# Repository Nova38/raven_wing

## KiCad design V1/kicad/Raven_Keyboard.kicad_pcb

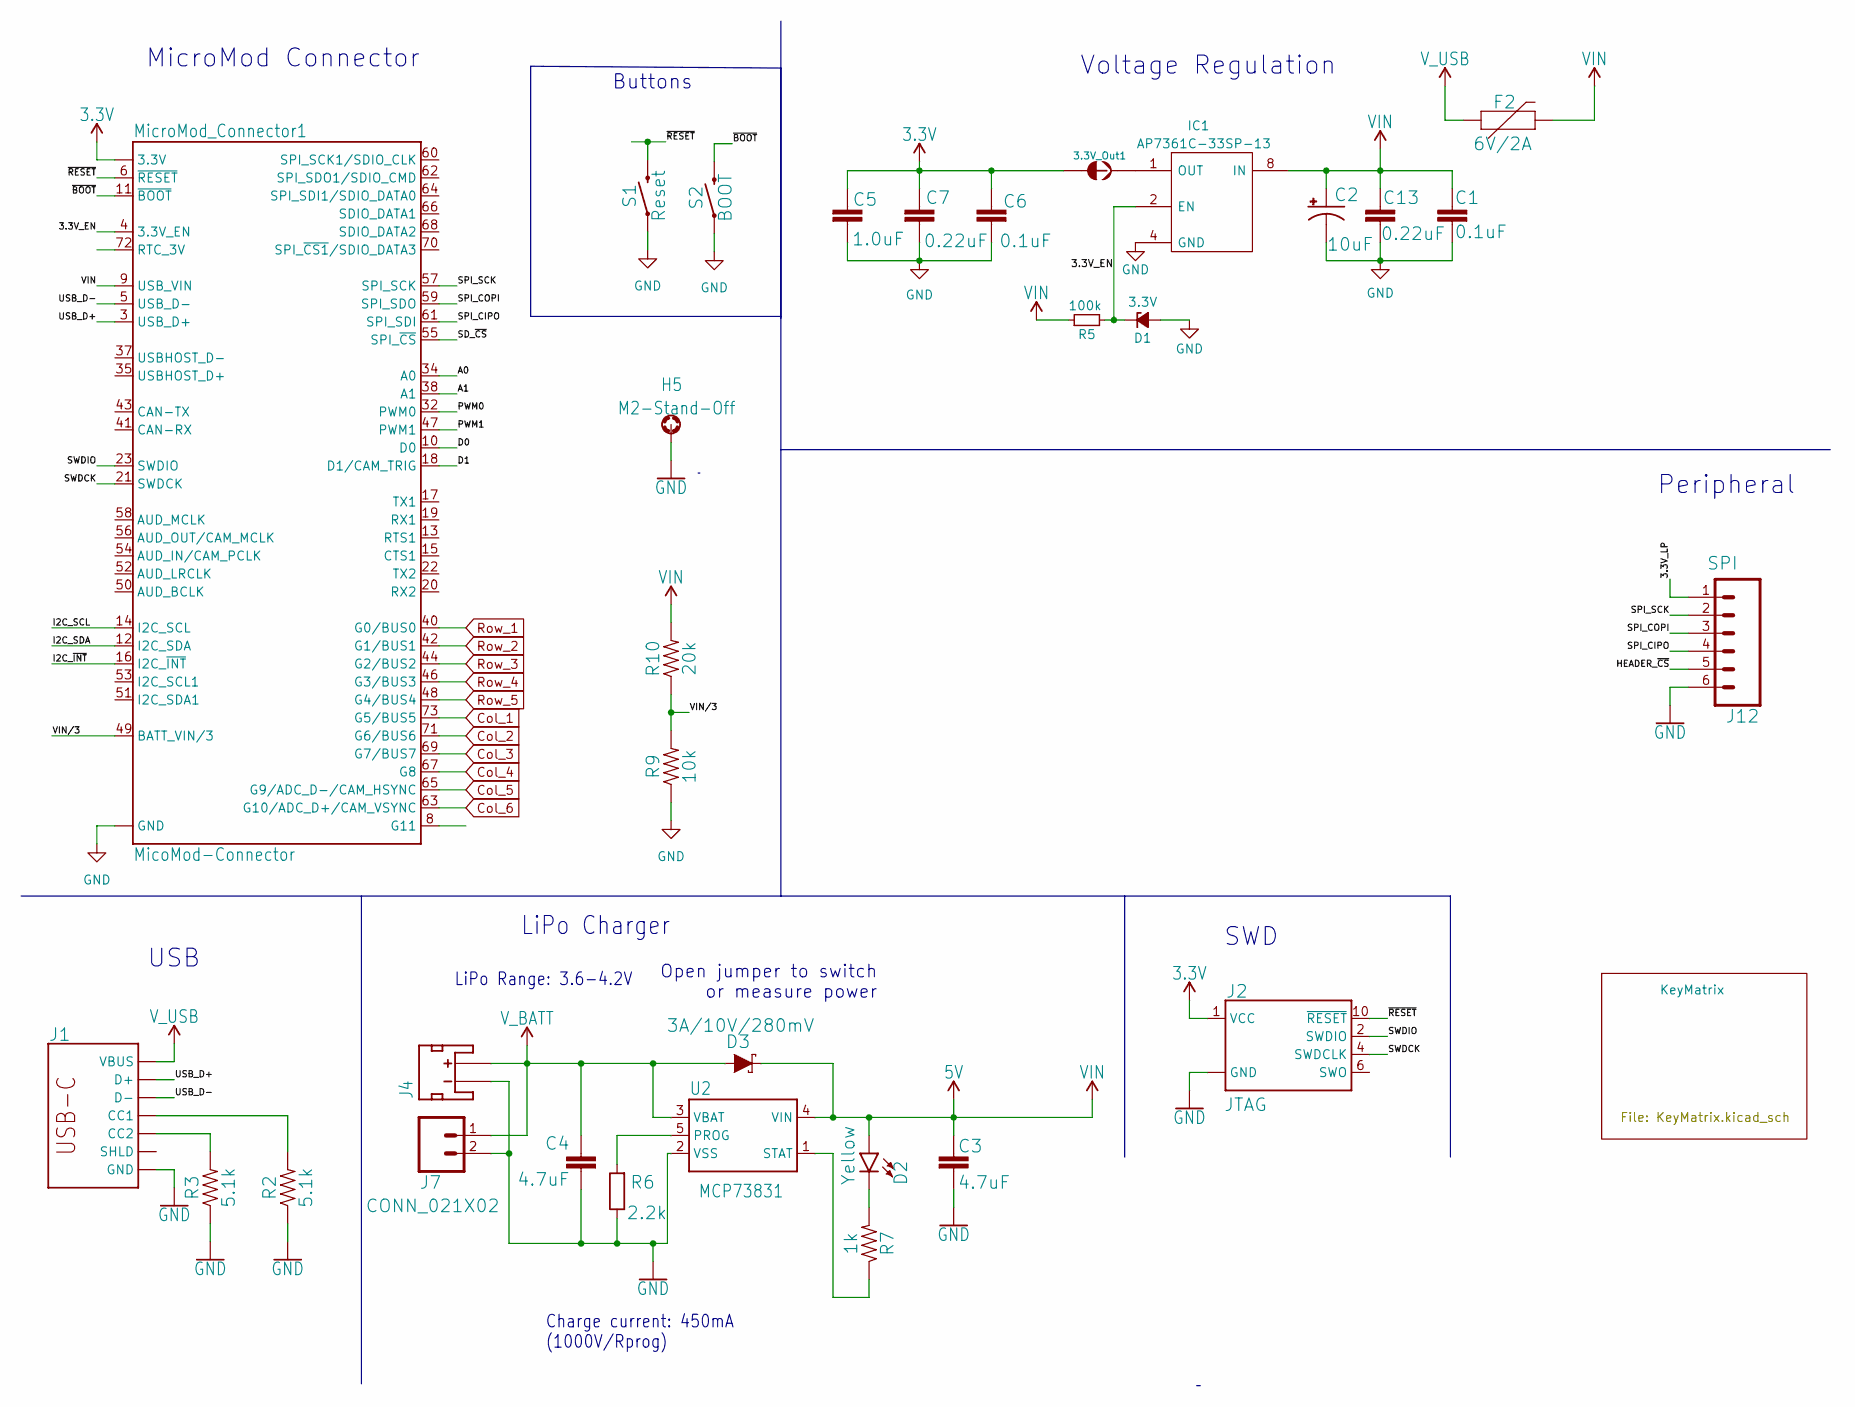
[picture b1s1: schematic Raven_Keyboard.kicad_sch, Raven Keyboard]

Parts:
3.3V_Out1: 3.3V Out; COMBO-JUMPER_2_NC_TRACE
C1, C6: 0.1uF; C_1206_3216Metric_Pad1.33x1.80mm_HandSolder
C2: 10uF; EIA3216
C3, C4: 4.7uF; 0603
C5: 1.0uF; C_1206_3216Metric_Pad1.33x1.80mm_HandSolder
C7, C13: 0.22uF; C_1206_3216Metric_Pad1.33x1.80mm_HandSolder
D1: 3.3V; D_1206_3216Metric_Pad1.42x1.75mm_HandSolder
D2: Yellow; LED-0603
D3: 3A/10V/280mV; SOD-323
F2: 6V/2A; 1210
H5: M2-Stand-Off; STAND-OFF-REFLOW-M2.5
IC1: AP7361C-33SP-13; SOIC127P600X163-9N; Mouser Part Number 621-AP7361C-33SP-13
J1: USB_C_2-LAYER_PADS; USB-C-16P-2LAYER-PADS
J2: JTAG; 2X5-PTH-1.27MM
J4: JST_2MM_MALE; JST-2-SMD
J7: CONN_021X02; 1X02_NO_SILK
J12: SPI; 1X06_NO_SILK
MicroMod_Connector1: MicoMod-Connector; M.2-CONNECTOR-E
R2, R3: 5.1k; 0603
R5: 100k; R_1206_3216Metric_Pad1.30x1.75mm_HandSolder
R6: 2.2k; 0603
R7: 1k; 0603
R9: 10k; 0603
R10: 20k; 0603
S1: Reset; TACTILE_SWITCH_SMD_5.2MM
S2: BOOT; TACTILE_SWITCH_SMD_5.2MM
U2: MCP73831; SOT23-5

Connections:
3.3V: 3.3V_Out1.1, 3.3V_Out1.3 (1), C5.1, C6.1, C7.1, J2.1 (VCC), MicroMod_Connector1.2 (3.3V), MicroMod_Connector1.74 (3.3V)
5V: C1.1, C2.+, C3.1, C13.1, D2.A, D3.C, F2.2, IC1.8 (IN), MicroMod_Connector1.9 (USB_VIN), R5.1, R10.2, U2.4 (VIN)
/3.3V_EN: D1.1 (K), IC1.2 (EN), MicroMod_Connector1.4 (3.3V_EN), R5.2
/3.3V_LP: J12.1
/A0: MicroMod_Connector1.34 (A0)
/A1: MicroMod_Connector1.38 (A1)
/D0: MicroMod_Connector1.10 (D0)
/D1: MicroMod_Connector1.18 (D1/CAM_TRIG)
/HEADER_~CS: J12.5
/I2C_SCL: MicroMod_Connector1.14 (I2C_SCL)
/I2C_SDA: MicroMod_Connector1.12 (I2C_SDA)
/I2C_~INT: MicroMod_Connector1.16 (I2C_~INT)
/PWM0: MicroMod_Connector1.32 (PWM0)
/PWM1: MicroMod_Connector1.47 (PWM1)
/SD_~CS: MicroMod_Connector1.55 (SPI_~CS)
/SPI_CIPO: J12.4, MicroMod_Connector1.61 (SPI_SDI)
/SPI_COPI: J12.3, MicroMod_Connector1.59 (SPI_SDO)
/SPI_SCK: J12.2, MicroMod_Connector1.57 (SPI_SCK)
/SWDCK: J2.4 (SWDCLK), MicroMod_Connector1.21 (SWDCK)
/SWDIO: J2.2 (SWDIO), MicroMod_Connector1.23 (SWDIO)
/USB_D+: J1.A6 (D+), J1.B6 (D+), MicroMod_Connector1.3 (USB_D+)
/USB_D-: J1.A7 (D-), J1.B7 (D-), MicroMod_Connector1.5 (USB_D-)
/VIN/3: MicroMod_Connector1.49 (BATT_VIN/3), R9.2, R10.1
/~BOOT: MicroMod_Connector1.11 (~BOOT), S2.3 (2), S2.4 (2)
/~RESET: J2.10 (~RESET), MicroMod_Connector1.6 (~RESET), S1.3 (2), S1.4 (2)
Col_1: MicroMod_Connector1.73 (G5/BUS5); also elsewhere on the board
Col_2: MicroMod_Connector1.71 (G6/BUS6); also elsewhere on the board
Col_3: MicroMod_Connector1.69 (G7/BUS7); also elsewhere on the board
Col_4: MicroMod_Connector1.67 (G8); also elsewhere on the board
Col_5: MicroMod_Connector1.65 (G9/ADC_D-/CAM_HSYNC); also elsewhere on the board
Col_6: MicroMod_Connector1.63 (G10/ADC_D+/CAM_VSYNC); also elsewhere on the board
GND: C1.2, C2.-, C3.2, C4.2, C5.2, C6.2, C7.2, C13.2, D1.2 (A), H5.1, IC1.4 (GND), J1.GND, J1.GND2 (GND), J2.3 (GND), J2.5 (GND), J2.9 (GND), J4.1 (-), J7.2, J12.6, MicroMod_Connector1.1 (GND), MicroMod_Connector1.7 (GND), MicroMod_Connector1.33 (GND), MicroMod_Connector1.36 (GND), MicroMod_Connector1.39 (GND), MicroMod_Connector1.45 (GND), MicroMod_Connector1.75 (GND), R2.1, R3.1, R6.1, R9.1, S1.1, S1.2 (1), S2.1, S2.2 (1), U2.2 (VSS)
unnamed: 3.3V_Out1.2, 3.3V_Out1.4 (2), IC1.1 (OUT)
unnamed: D2.C, R7.2
unnamed: J1.A5 (CC1), R2.2
unnamed: J1.B5 (CC2), R3.2
unnamed: J1.SHLD1 (SHLD), J1.SHLD2 (SHLD), J1.SHLD3 (SHLD), J1.SHLD4 (SHLD)
unnamed: R6.2, U2.5 (PROG)
unnamed: R7.1, U2.1 (STAT)
Row_1: MicroMod_Connector1.40 (G0/BUS0); also elsewhere on the board
Row_2: MicroMod_Connector1.42 (G1/BUS1); also elsewhere on the board
Row_3: MicroMod_Connector1.44 (G2/BUS2); also elsewhere on the board
Row_4: MicroMod_Connector1.46 (G3/BUS3); also elsewhere on the board
Row_5: MicroMod_Connector1.48 (G4/BUS4); also elsewhere on the board
V_BATT: C4.1, D3.A, J4.2 (+), J7.1, U2.3 (VBAT)
V_USB: F2.1, J1.VBUS1 (VBUS), J1.VBUS2 (VBUS)

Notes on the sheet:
LiPo Range: 3.6-4.2V
SWD
Peripheral
Charge current: 450mA (1000V/Rprog)
USB
Open jumper to switch or measure power
LiPo Charger
Buttons
Voltage Regulation
MicroMod Connector

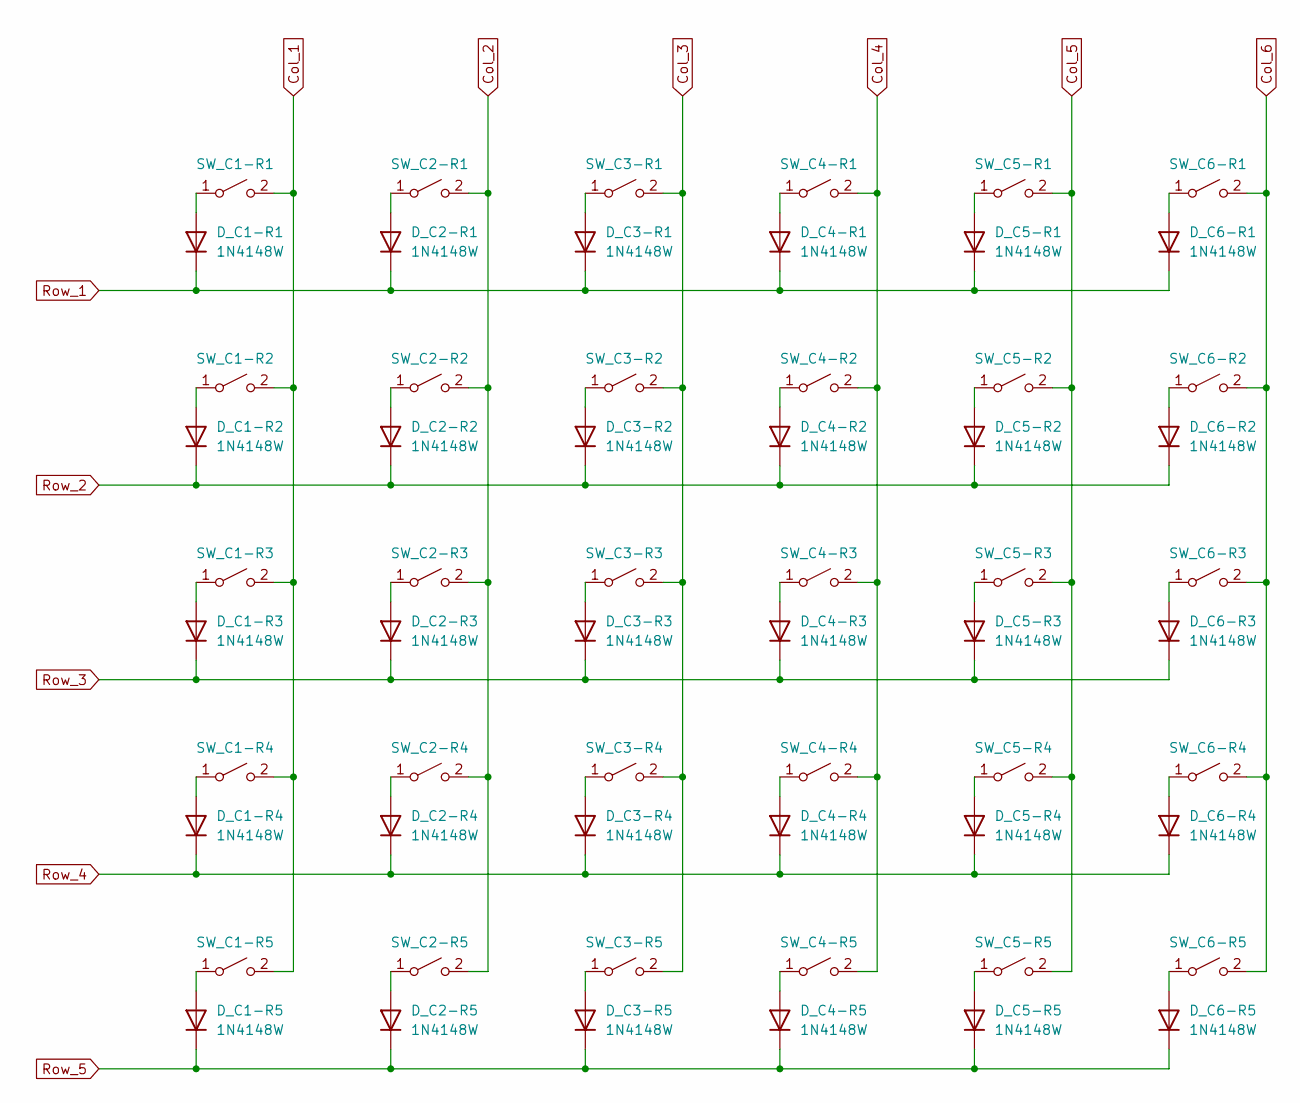
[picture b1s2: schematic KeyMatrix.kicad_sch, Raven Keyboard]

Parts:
D_C1-R1, D_C1-R2, D_C1-R3, D_C1-R4, D_C1-R5, D_C2-R1, D_C2-R2, D_C2-R3, D_C2-R4, D_C2-R5, D_C3-R1, D_C3-R2, D_C3-R3, D_C3-R4, D_C3-R5, D_C4-R1, D_C4-R2, D_C4-R3, D_C4-R4, D_C4-R5, D_C5-R1, D_C5-R2, D_C5-R3, D_C5-R4, D_C5-R5, D_C6-R1, D_C6-R2, D_C6-R3, D_C6-R4, D_C6-R5: 1N4148W; D_SOD-123
SW_C1-R1, SW_C1-R2, SW_C1-R3, SW_C1-R4, SW_C1-R5, SW_C2-R1, SW_C2-R2, SW_C2-R3, SW_C2-R4, SW_C2-R5, SW_C3-R1, SW_C3-R2, SW_C3-R3, SW_C3-R4, SW_C3-R5, SW_C4-R1, SW_C4-R2, SW_C4-R3, SW_C4-R4, SW_C4-R5, SW_C5-R1, SW_C5-R2, SW_C5-R3, SW_C5-R4, SW_C5-R5, SW_C6-R1, SW_C6-R2, SW_C6-R3, SW_C6-R4, SW_C6-R5: SW_Kailh_Choc_V1_1.00u

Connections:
Col_1: SW_C1-R1.2 (B), SW_C1-R2.2 (B), SW_C1-R3.2 (B), SW_C1-R4.2 (B), SW_C1-R5.2 (B); also elsewhere on the board
Col_2: SW_C2-R1.2 (B), SW_C2-R2.2 (B), SW_C2-R3.2 (B), SW_C2-R4.2 (B), SW_C2-R5.2 (B); also elsewhere on the board
Col_3: SW_C3-R1.2 (B), SW_C3-R2.2 (B), SW_C3-R3.2 (B), SW_C3-R4.2 (B), SW_C3-R5.2 (B); also elsewhere on the board
Col_4: SW_C4-R1.2 (B), SW_C4-R2.2 (B), SW_C4-R3.2 (B), SW_C4-R4.2 (B), SW_C4-R5.2 (B); also elsewhere on the board
Col_5: SW_C5-R1.2 (B), SW_C5-R2.2 (B), SW_C5-R3.2 (B), SW_C5-R4.2 (B), SW_C5-R5.2 (B); also elsewhere on the board
Col_6: SW_C6-R1.2 (B), SW_C6-R2.2 (B), SW_C6-R3.2 (B), SW_C6-R4.2 (B), SW_C6-R5.2 (B); also elsewhere on the board
unnamed: D_C1-R1.2 (A), SW_C1-R1.1 (A)
unnamed: D_C1-R2.2 (A), SW_C1-R2.1 (A)
unnamed: D_C1-R3.2 (A), SW_C1-R3.1 (A)
unnamed: D_C1-R4.2 (A), SW_C1-R4.1 (A)
unnamed: D_C1-R5.2 (A), SW_C1-R5.1 (A)
unnamed: D_C2-R1.2 (A), SW_C2-R1.1 (A)
unnamed: D_C2-R2.2 (A), SW_C2-R2.1 (A)
unnamed: D_C2-R3.2 (A), SW_C2-R3.1 (A)
unnamed: D_C2-R4.2 (A), SW_C2-R4.1 (A)
unnamed: D_C2-R5.2 (A), SW_C2-R5.1 (A)
unnamed: D_C3-R1.2 (A), SW_C3-R1.1 (A)
unnamed: D_C3-R2.2 (A), SW_C3-R2.1 (A)
unnamed: D_C3-R3.2 (A), SW_C3-R3.1 (A)
unnamed: D_C3-R4.2 (A), SW_C3-R4.1 (A)
unnamed: D_C3-R5.2 (A), SW_C3-R5.1 (A)
unnamed: D_C4-R1.2 (A), SW_C4-R1.1 (A)
unnamed: D_C4-R2.2 (A), SW_C4-R2.1 (A)
unnamed: D_C4-R3.2 (A), SW_C4-R3.1 (A)
unnamed: D_C4-R4.2 (A), SW_C4-R4.1 (A)
unnamed: D_C4-R5.2 (A), SW_C4-R5.1 (A)
unnamed: D_C5-R1.2 (A), SW_C5-R1.1 (A)
unnamed: D_C5-R2.2 (A), SW_C5-R2.1 (A)
unnamed: D_C5-R3.2 (A), SW_C5-R3.1 (A)
unnamed: D_C5-R4.2 (A), SW_C5-R4.1 (A)
unnamed: D_C5-R5.2 (A), SW_C5-R5.1 (A)
unnamed: D_C6-R1.2 (A), SW_C6-R1.1 (A)
unnamed: D_C6-R2.2 (A), SW_C6-R2.1 (A)
unnamed: D_C6-R3.2 (A), SW_C6-R3.1 (A)
unnamed: D_C6-R4.2 (A), SW_C6-R4.1 (A)
unnamed: D_C6-R5.2 (A), SW_C6-R5.1 (A)
Row_1: D_C1-R1.1 (K), D_C2-R1.1 (K), D_C3-R1.1 (K), D_C4-R1.1 (K), D_C5-R1.1 (K), D_C6-R1.1 (K); also elsewhere on the board
Row_2: D_C1-R2.1 (K), D_C2-R2.1 (K), D_C3-R2.1 (K), D_C4-R2.1 (K), D_C5-R2.1 (K), D_C6-R2.1 (K); also elsewhere on the board
Row_3: D_C1-R3.1 (K), D_C2-R3.1 (K), D_C3-R3.1 (K), D_C4-R3.1 (K), D_C5-R3.1 (K), D_C6-R3.1 (K); also elsewhere on the board
Row_4: D_C1-R4.1 (K), D_C2-R4.1 (K), D_C3-R4.1 (K), D_C4-R4.1 (K), D_C5-R4.1 (K), D_C6-R4.1 (K); also elsewhere on the board
Row_5: D_C1-R5.1 (K), D_C2-R5.1 (K), D_C3-R5.1 (K), D_C4-R5.1 (K), D_C5-R5.1 (K), D_C6-R5.1 (K); also elsewhere on the board

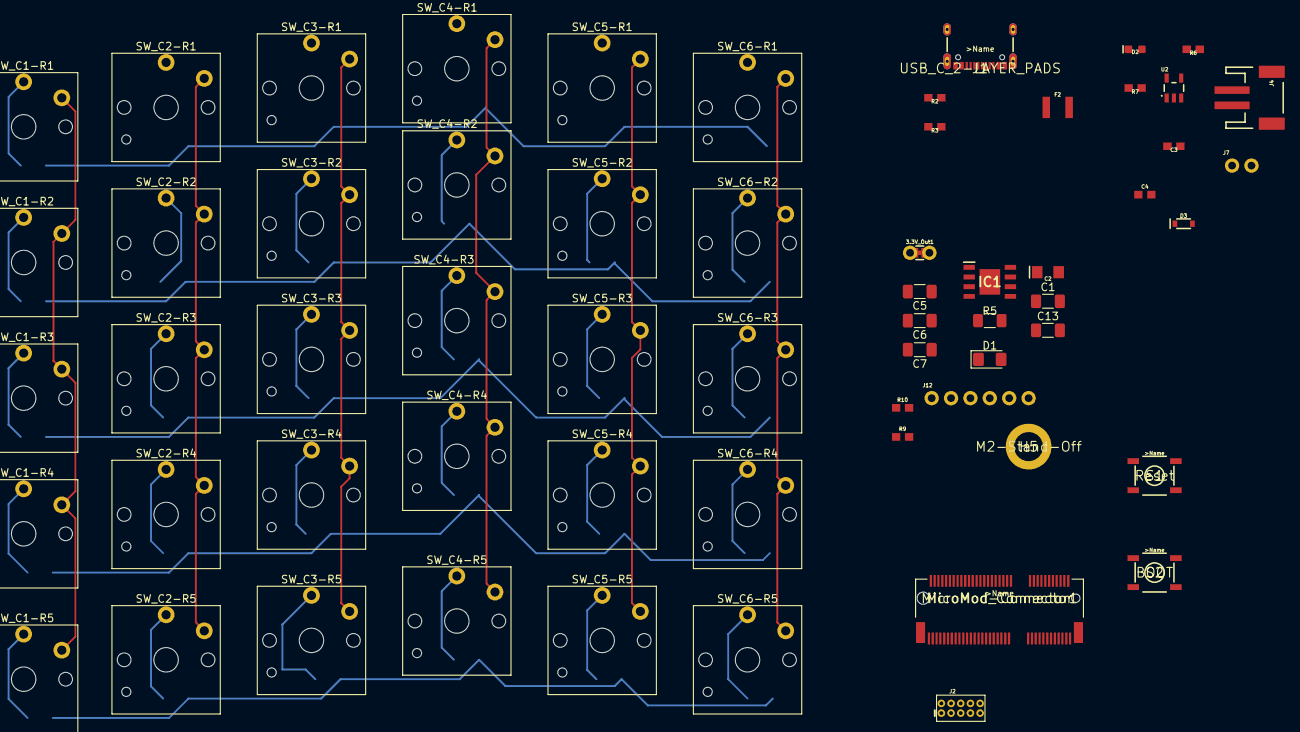
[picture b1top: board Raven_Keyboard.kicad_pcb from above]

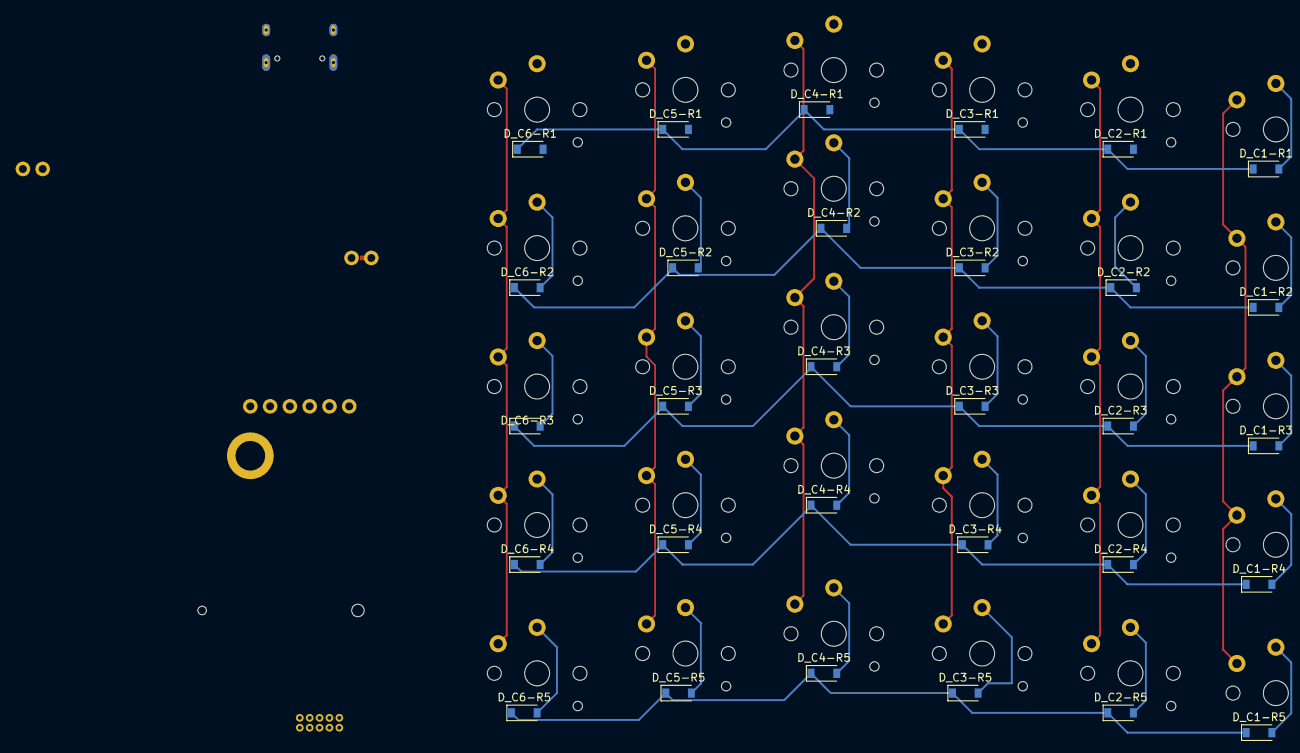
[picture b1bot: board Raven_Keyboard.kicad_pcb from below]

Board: 2 copper layers, 91 parts (30 on the bottom side), 64 nets.

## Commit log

2021-12-27 made inital files for github action
2021-12-27 inital setup
2022-01-01 added kicad stuff
2022-01-19 worked on kicad
